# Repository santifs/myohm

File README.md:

# Myohm

Research and teaching platform for bioimpedance measurement: nRF5340, AD5941 and nPM1304.

**Research instrument, not a medical device. It has not been assessed against IEC 60601-1; measure people only within an ethics-approved research protocol, on battery power, after reading [Safety](#safety). Original hardware is licensed under CERN-OHL-S-2.0 and original software under Apache-2.0; bench data under CC-BY-4.0. Third-party libraries, models and vendor code keep their original terms; see [licence scope](LICENSE.md).**

| Component side | Rear silkscreen |
| :---: | :---: |
|  |  |

## Start here

- [Licence scope](LICENSE.md)
- [Engineering audit and blockers](docs/hardware-audit.md)
- [Licensing choices and third-party provenance](docs/licensing.md)
- [Validation and release gates](docs/validation.md)
- [Hardware sources](hardware/README.md)
- [Firmware](firmware/README.md) and [BLE protocol](firmware/nrf5340_zephyr/docs/ble-protocol.md)
- [Teaching laboratory](web/README.md)
- [Local-only iOS and Android clients](mobile/README.md)
- [Published Myohm workbench](https://lab.santiagofs.com/myohm/)

## Design and bench data

| Resource | Repository |
| --- | --- |
| Main board and electrode strips (75, 100, 150 mm; 50 mm designed) | `hardware/mainboard`, `hardware/electrodes` |
| Firmware, BLE protocol, sweep 4–198 kHz | `firmware/nrf5340_zephyr` |
| Bench procedure with the AD5940 impedance test board | `tools/bench/ztest.py` |
| Bench measurements | `tools/bench/data` (CC-BY-4.0) |
| Bench error model | `tools/bench/bench_error_model.py`, output `bench_error_model.json` |
| Nodal model of contact-impedance errors | `tools/bench/mismatch_model.py` |
| Sweep quality control, R/Xc and Cole fitting | `tools/analysis/myohm_spectra.py` |
| Android and iOS clients | `mobile/` |

## Interpreting a Cole fit

The Python analysis fits the real and imaginary parts of the aggregated impedance together.
Frequencies are in Hz, resistances are in ohms, and `tau_s` is in seconds.
In the denominator `1 + (j 2π f τ)^p`, use `p = cole_exponent`.
This is the exponent called alpha in the mobile models and the [Swarthmore MATLAB implementation](https://github.com/santifs/swarthmore/blob/2d40aa04922a031763f097dffae03454ec257618/matlab/Helpers%20Across%20Projects/fitColeColeModelMultiStartLevMar.m).
The Python field `alpha` retains the BioMess dispersion convention, so `p = 1 - alpha`.

Read `quality_flag` for repeat-sweep consistency, `success` for solver termination, and
`accepted` for the fit decision. A converged fit can still fail the acceptance criteria.
`rmse_pct` is 100 times the RMS complex residual divided by mean measured magnitude.
`cost_spread` is the range of solver costs across starts. It is not a parameter uncertainty.
The mobile optimizers use magnitude residuals. New mobile fit error percentages use the RMS
magnitude residual divided by mean measured magnitude, multiplied by 100. Older mobile
records can contain an ohm-valued residual in the percentage field. The quick mobile estimate
uses the sampled reactance peak and assumes an exponent of 0.8.

An unavailable Python estimate is JSON `null`; `failure_reason` explains a rejected fit.

## Safety

- The default excitation (800 mV peak-to-peak waveform, excitation-buffer gain 2) gives 1.6 V peak-to-peak behind 1 kΩ: up to 0.57 mA rms into a short circuit, and an output outside the ±607 mV range specified for the AD5941.
- The IEC 60601-1 patient auxiliary current limit for type BF parts (100 µA rms, rising with frequency above 1 kHz) is met by the short-circuit current only above about 5.7 kHz.
- For on-body use, build the firmware with `CONFIG_MYOHM_EXCITATION_MVPP=500` (0.35 mA rms into a short circuit). The default stays at 800 mV because the published bench data were acquired with it.
- Leakage, single-fault and charger behaviour have not been measured. Disconnect USB, SWD and bench instruments before connecting a person.
- Contact impedance limits accuracy. Several kilohms at a current electrode degrade the high-frequency phase, and kilohms at a voltage electrode can invalidate the measurement. The firmware's contact check (`0x0B`, see the [BLE protocol](firmware/nrf5340_zephyr/docs/ble-protocol.md)) is experimental and not yet validated on hardware.

## Repository layout

| Directory | Contents |
| --- | --- |
| `hardware/mainboard` | KiCad 10 project, schematic, PCB and local footprints |
| `hardware/3D` | Manufacturer component models, original terms |
| `hardware/library` | Recovered editable symbols and footprints |
| `firmware/nrf5340_zephyr` | Application and out-of-tree board; nRF Connect SDK 3.3.0 |
| `web` | React teaching lab, BLE transport and offline calculations |
| `mobile` | Native iOS and Android clients; local storage and explicit export |
| `docs` | Requirements, audit, provenance and release process |
| `tools` | Repository and hardware checks; `tools/bench` bench procedure, data and models; `tools/analysis` spectral analysis |
| `reports` | Review evidence, not production manufacturing files |

The repository starts from the corrected mainboard working tree and active firmware. The source candidate excludes experimental subject data, papers, experimental mobile applications, old nRF52832 hardware and build caches. Electrode fabrication exports are experimental review artifacts; no production mainboard Gerbers are supplied. See [source manifest](docs/import-manifest.json). Legacy identifiers (`AllInOne`, `BioMess`, `biomess_nrf5340`) remain where changing them would affect hardware revision identification or software compatibility. Myohm is the project name; a branding migration must preserve the BLE wire protocol.

## Checks

```sh
python3 tools/check_repository.py
python3 tools/verify_firmware_offline.py
python3 tools/check_hardware.py  # requires KiCad 10; ERC currently fails honestly
cd web
npm ci
npm test
npm run build
```

Source: https://github.com/santifs/myohm. A clean DRC is not electrical, RF, battery or human-use validation.

La [revisión eléctrica del 20 de septiembre](docs/electrical-review.md) registra las primeras correcciones de símbolos, las comprobaciones de integridad y las decisiones de diseño pendientes.

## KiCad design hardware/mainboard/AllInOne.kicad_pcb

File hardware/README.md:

# Myohm hardware

Current PCB v2 candidate: nRF5340 / AD5941 / nPM1304, imported from the `AllInOne-corrected` hardware working tree. This is not the old nRF52832/BQ24074 board.

Open `mainboard/AllInOne.kicad_pro` with KiCad 10.0.3 and standard KiCad 10 footprint/3D libraries installed. Project libraries use `${KIPRJMOD}`. Recovered symbols started from imported definitions; the electrical review records subsequent pin-type corrections. Editable does not mean fully validated. Footprint filters include the assigned KiCad names in addition to imported Altium names; this is metadata migration, not dimensional approval.

Firmware target: `biomess_nrf5340/nrf5340/cpuapp`. [Pinout](../firmware/nrf5340_zephyr/docs/hardware-v2.md), [audit](../docs/hardware-audit.md).

The historical `BOM.csv` is a reference only; use the generated schematic inventory in reports for review. Missing manufacturer part numbers and unknown battery remain release blockers. No production Gerbers are included, because inherited Gerbers predate the corrected board.

Original hardware contributions: **CERN-OHL-S-2.0**, with [scope and third-party exclusions](LICENSE.md).

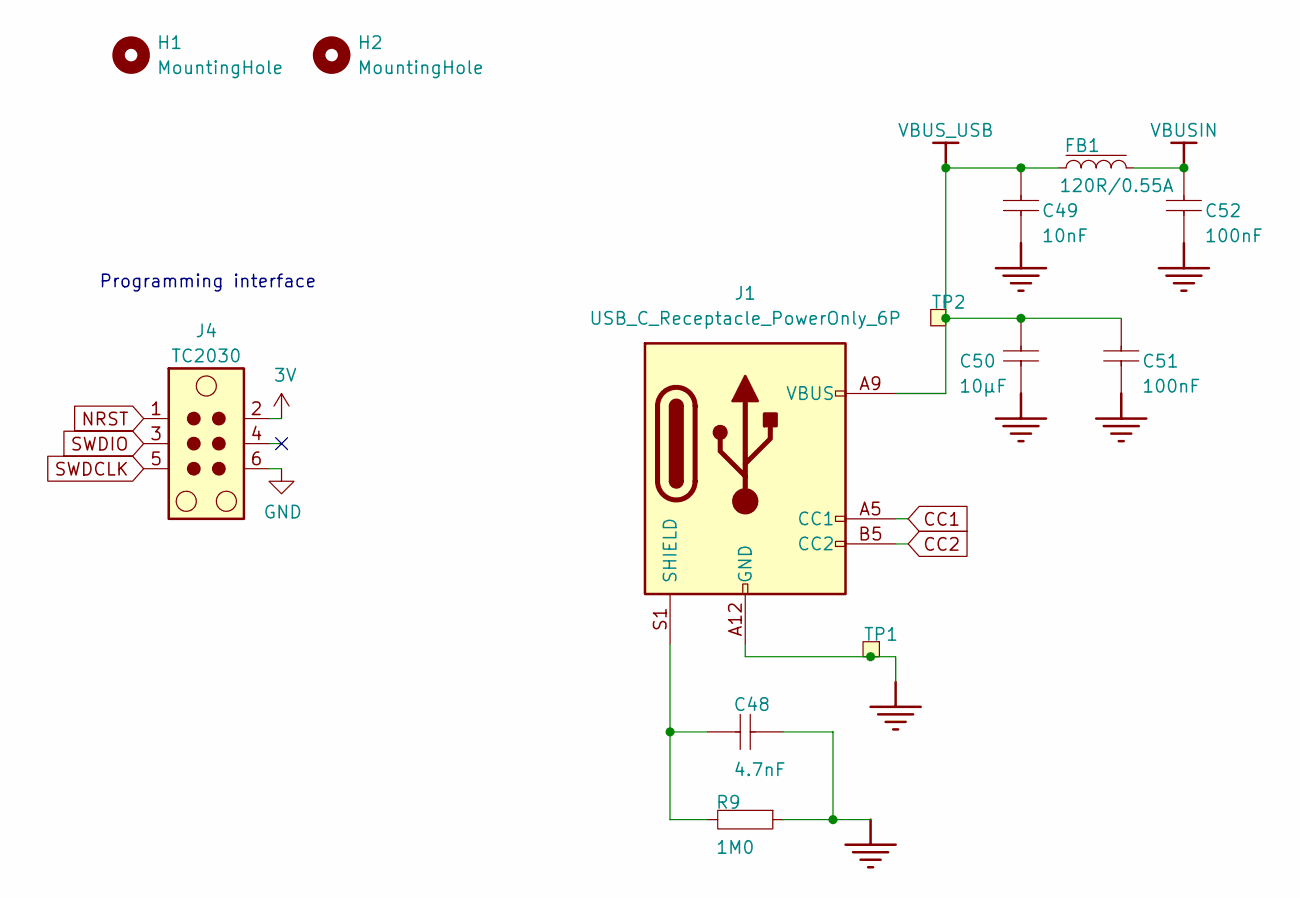
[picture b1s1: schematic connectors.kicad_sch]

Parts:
C48: 4.7nF; C_0201_0603Metric; PART NUMBER C0201-4n7-25V-X5R
C49: 10nF; C_0201_0603Metric; PART NUMBER C0201-10n-25V-X5R
C50: 10µF; C_0603_1608Metric; PART NUMBER C0603-10µ-25V-X5R-GRM188R61E106MA73J
C51, C52: 100nF; C_0201_0603Metric; PART NUMBER C0201-100n-25V-X5R
FB1: 120R/0.55A; L_0402_1005Metric; PART NUMBER FB0402-120R@100M-500mA
H1, H2: MountingHole; MountingHole_2.2mm_M2
J1: USB_C_Receptacle_PowerOnly_6P; USB_C_Receptacle_GCT_USB4135-GF-A_6P_TopMnt_Horizontal
J4: TC2030; Tag-Connect_TC2030-IDC-NL_2x03_P1.27mm_Vertical
R9: 1M0; R_0201_0603Metric; PART NUMBER R0201-1M0
TP1, TP2: Ø1.5mm,SMD; TestPoint_Pad_D1.5mm; PART NUMBER TP_SMD_Ø1.5MM

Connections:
AVDD_2: J4.2; also elsewhere on the board
CC1: J1.A5 (CC1); also elsewhere on the board
CC2: J1.B5 (CC2); also elsewhere on the board
GND: C48.2, C49.1, C50.1, C51.1, C52.1, J1.A12 (GND), J1.B12 (GND), J4.6, R9.2, TP1.1 (1_1); also elsewhere on the board
NRST: J4.1; also elsewhere on the board
unnamed: C48.1, J1.S1 (SHIELD), R9.1
SWDCLK: J4.5; also elsewhere on the board
SWDIO: J4.3; also elsewhere on the board
VBUSIN: C52.2, FB1.2; also elsewhere on the board
VBUS_USB: C49.2, C50.2, C51.2, FB1.1, J1.A9 (VBUS), J1.B9 (VBUS), TP2.1 (1_1)

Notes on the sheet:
Programming interface

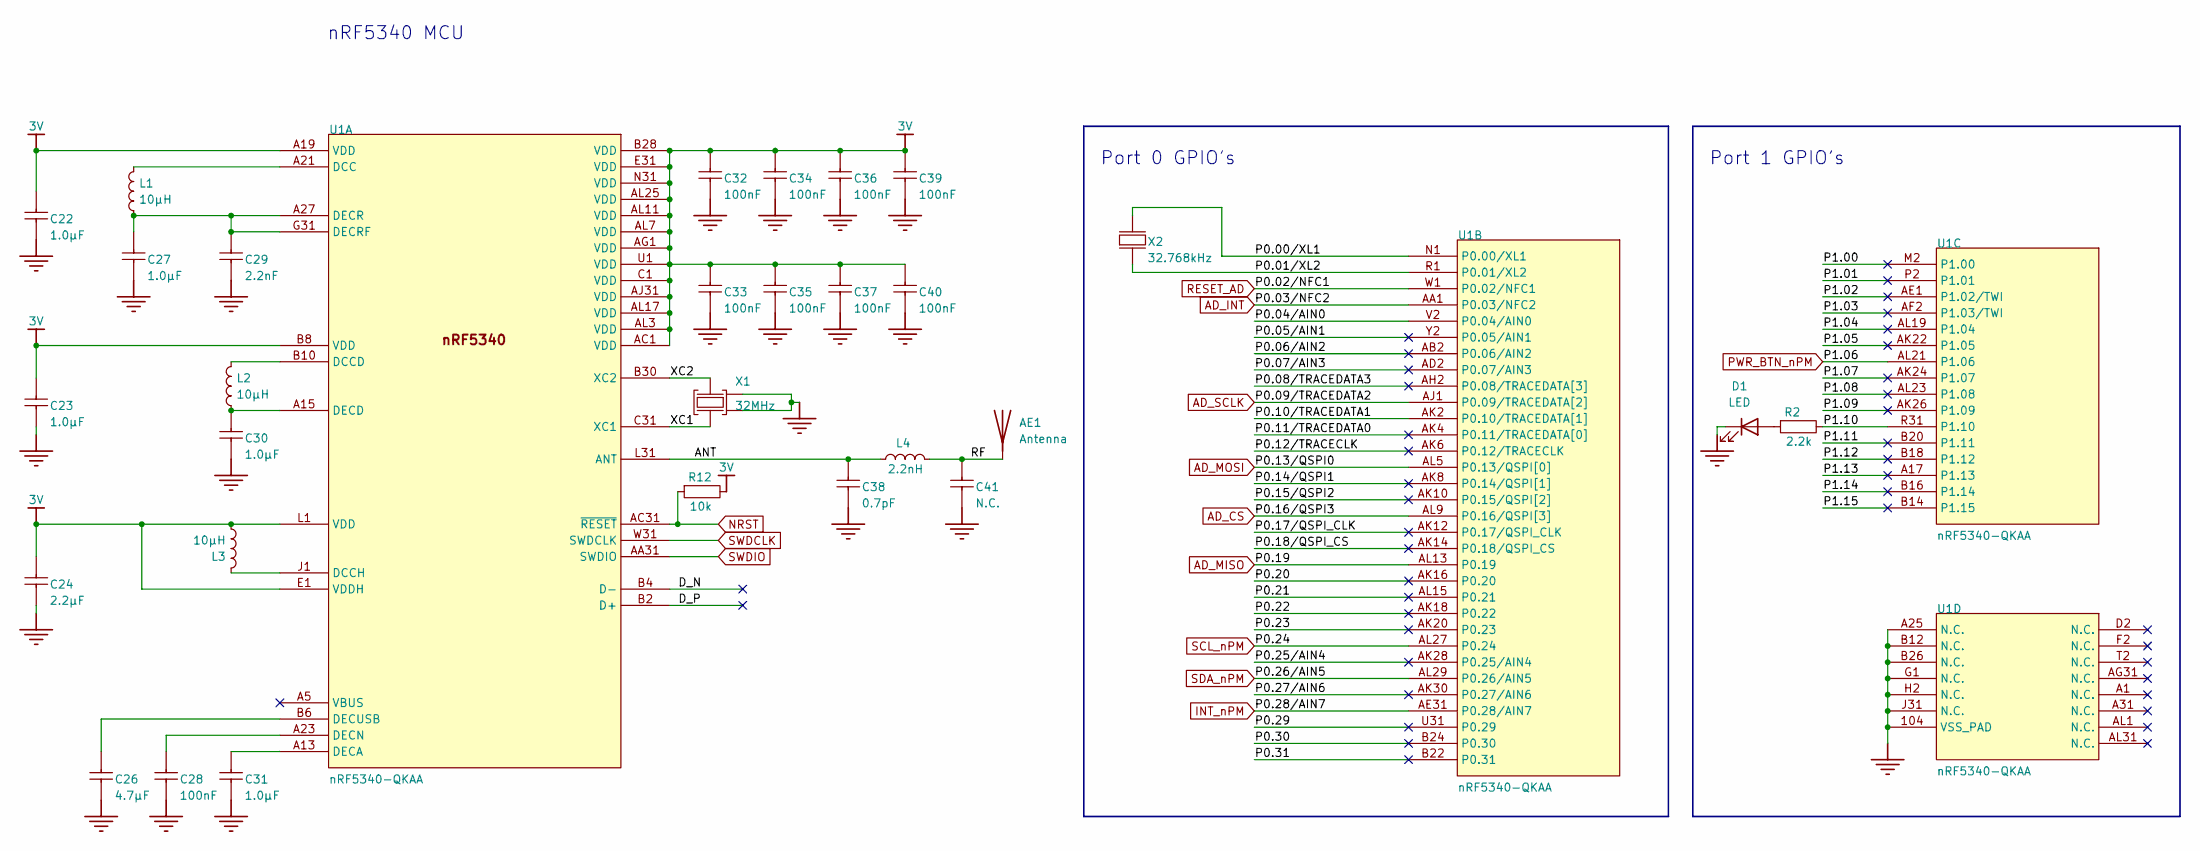
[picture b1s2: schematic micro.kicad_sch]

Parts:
AE1: Antenna; Johanson_2450AT18x100
C22, C23, C27, C30, C31: 1.0µF; C_0402_1005Metric; PART NUMBER C0402-1µ0-25V-X5R
C24: 2.2µF; C_0402_1005Metric; PART NUMBER C0402-1µ0-25V-X5R
C26: 4.7µF; C_0603_1608Metric; PART NUMBER C0603-4µ7-25V-X5R
C28, C32, C33, C34, C35, C36, C37, C39, C40: 100nF; C_0201_0603Metric; PART NUMBER C0201-100n-6.3V-X5R
C29: 2.2nF; C_0201_0603Metric; PART NUMBER C0201-2n2-10V-X5R
C38: 0.7pF; C_0201_0603Metric; PART NUMBER C0201-0.7p-50V-C0G-GJM0335C1HR70WB01
C41: N.C.; C_0402_1005Metric; PART NUMBER C0201-N.C.
D1: LED; LED_0603_1608Metric
L1, L2, L3: 10µH; L_0603_1608Metric; PART NUMBER L0603-10µ-Murata-DN
L4: 2.2nH; L_0201_0603Metric; PART NUMBER L0201-2n2-HQ-Murata
R2: 2.2k; R_0402_1005Metric; MANUFACTURER PART NUMBER N.A.
R12: 10k; R_0201_0603Metric; PART NUMBER R0201-47k
U1: nRF5340-QKAA; nRF5340-QKAA-Messi; PART NUMBER nRF5340-QKAAD0
X1: 32MHz; Crystal_SMD_2016-4Pin_2.0x1.6mm; PART NUMBER XRCGB32M000F1S1BR0
X2: 32.768kHz; Crystal_SMD_2012-2Pin_2.0x1.2mm; PART NUMBER XTAL_SMD2012_32.768kHz_9pF_MC

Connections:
/Micro/ANT: C38.2, L4.2, U1.L31 (ANT)
/Micro/D_N: U1.B4 (D-)
/Micro/D_P: U1.B2 (D+)
/Micro/P0.00/XL1: U1.N1 (P0.00/XL1), X2.1 (inp)
/Micro/P0.01/XL2: U1.R1 (P0.01/XL2), X2.2 (out)
/Micro/P0.04/AIN0: U1.V2 (P0.04/AIN0)
/Micro/P0.05/AIN1: U1.Y2 (P0.05/AIN1)
/Micro/P0.06/AIN2: U1.AB2 (P0.06/AIN2)
/Micro/P0.07/AIN3: U1.AD2 (P0.07/AIN3)
/Micro/P0.08/TRACEDATA3: U1.AH2 (P0.08/TRACEDATA[3])
/Micro/P0.10/TRACEDATA1: U1.AK2 (P0.10/TRACEDATA[1])
/Micro/P0.11/TRACEDATA0: U1.AK4 (P0.11/TRACEDATA[0])
/Micro/P0.12/TRACECLK: U1.AK6 (P0.12/TRACECLK)
/Micro/P0.14/QSPI1: U1.AK8 (P0.14/QSPI[1])
/Micro/P0.15/QSPI2: U1.AK10 (P0.15/QSPI[2])
/Micro/P0.17/QSPI_CLK: U1.AK12 (P0.17/QSPI_CLK)
/Micro/P0.18/QSPI_CS: U1.AK14 (P0.18/QSPI_CS)
/Micro/P0.20: U1.AK16 (P0.20)
/Micro/P0.21: U1.AL15 (P0.21)
/Micro/P0.22: U1.AK18 (P0.22)
/Micro/P0.23: U1.AK20 (P0.23)
/Micro/P0.25/AIN4: U1.AK28 (P0.25/AIN4)
/Micro/P0.27/AIN6: U1.AK30 (P0.27/AIN6)
/Micro/P0.29: U1.U31 (P0.29)
/Micro/P0.30: U1.B24 (P0.30)
/Micro/P0.31: U1.B22 (P0.31)
/Micro/P1.00: U1.M2 (P1.00)
/Micro/P1.01: U1.P2 (P1.01)
/Micro/P1.02: U1.AE1 (P1.02/TWI)
/Micro/P1.03: U1.AF2 (P1.03/TWI)
/Micro/P1.04: U1.AL19 (P1.04)
/Micro/P1.05: U1.AK22 (P1.05)
/Micro/P1.07: U1.AK24 (P1.07)
/Micro/P1.08: U1.AL23 (P1.08)
/Micro/P1.09: U1.AK26 (P1.09)
/Micro/P1.10: R2.1, U1.R31 (P1.10)
/Micro/P1.11: U1.B20 (P1.11)
/Micro/P1.12: U1.B18 (P1.12)
/Micro/P1.13: U1.A17 (P1.13)
/Micro/P1.14: U1.B16 (P1.14)
/Micro/P1.15: U1.B14 (P1.15)
/Micro/RF: AE1.1 (A_1), C41.2, L4.1
/Micro/XC1: U1.C31 (XC1), X1.1 (IN)
/Micro/XC2: U1.B30 (XC2), X1.3 (OUT)
AD_CS: U1.AL9 (P0.16/QSPI[3]); also elsewhere on the board
AD_INT: U1.AA1 (P0.03/NFC2); also elsewhere on the board
AD_MISO: U1.AL13 (P0.19); also elsewhere on the board
AD_MOSI: U1.AL5 (P0.13/QSPI[0]); also elsewhere on the board
AD_SCLK: U1.AJ1 (P0.09/TRACEDATA[2]); also elsewhere on the board
AVDD_2: C22.1, C23.2, C24.2, C32.1, C33.1, C34.1, C35.1, C36.1, C37.1, C39.1, C40.1, L3.1, R12.1, U1.A19 (VDD), U1.AC1 (VDD), U1.AG1 (VDD), U1.AJ31 (VDD), U1.AL3 (VDD), U1.AL7 (VDD), U1.AL11 (VDD), U1.AL17 (VDD), U1.AL25 (VDD), U1.B8 (VDD), U1.B28 (VDD), U1.C1 (VDD), U1.E1 (VDDH), U1.E31 (VDD), U1.L1 (VDD), U1.N31 (VDD), U1.U1 (VDD); also elsewhere on the board
GND: C22.2, C23.1, C24.1, C26.2, C27.1, C28.2, C29.2, C30.1, C31.1, C32.2, C33.2, C34.2, C35.2, C36.2, C37.2, C38.1, C39.2, C40.2, C41.1, D1.1 (K), U1.104 (VSS_PAD), U1.A25 (N.C.), U1.B12 (N.C.), U1.B26 (N.C.), U1.G1 (N.C.), U1.H2 (N.C.), U1.J31 (N.C.), X1.2 (GND), X1.4 (GND); also elsewhere on the board
INT_nPM: U1.AE31 (P0.28/AIN7); also elsewhere on the board
NRST: R12.2, U1.AC31 (~RESET); also elsewhere on the board
unnamed: D1.2 (A), R2.2
unnamed: L1.2, U1.A21 (DCC)
unnamed: L2.2, U1.B10 (DCCD)
unnamed: L3.2, U1.J1 (DCCH)
unnamed: C31.2, U1.A13 (DECA)
unnamed: C30.2, L2.1, U1.A15 (DECD)
unnamed: C28.1, U1.A23 (DECN)
unnamed: C27.2, C29.1, L1.1, U1.A27 (DECR), U1.G31 (DECRF)
unnamed: C26.1, U1.B6 (DECUSB)
PWR_BTN_nPM: U1.AL21 (P1.06); also elsewhere on the board
RESET_AD: U1.W1 (P0.02/NFC1); also elsewhere on the board
SCL_nPM: U1.AL27 (P0.24); also elsewhere on the board
SDA_nPM: U1.AL29 (P0.26/AIN5); also elsewhere on the board
SWDCLK: U1.W31 (SWDCLK); also elsewhere on the board
SWDIO: U1.AA31 (SWDIO); also elsewhere on the board

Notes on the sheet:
Port 0 GPIO's
Port 1 GPIO's
nRF5340 MCU

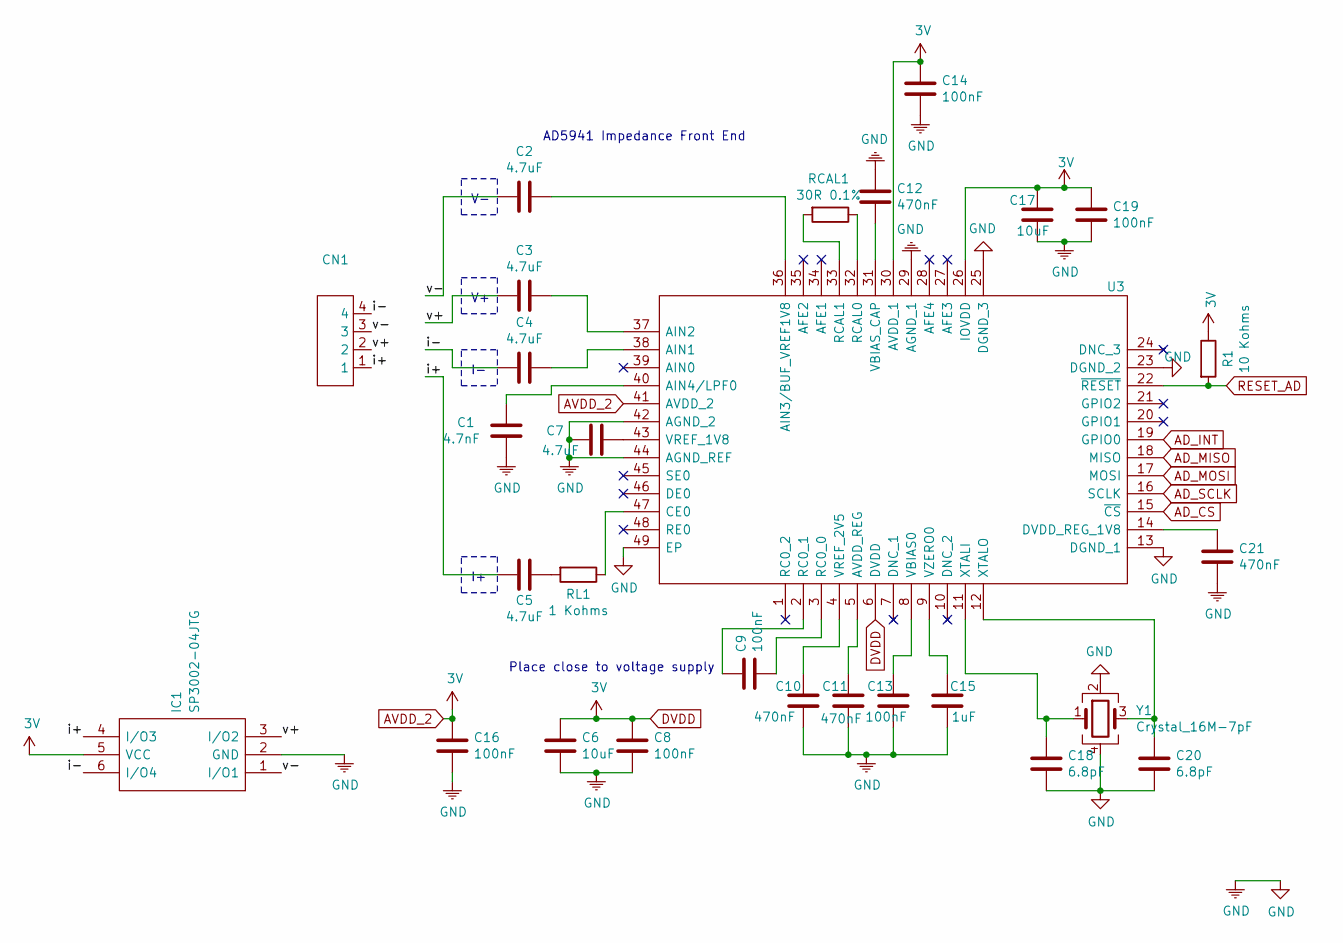
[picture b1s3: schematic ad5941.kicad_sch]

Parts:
C1: 4.7nF; C_0603_1608Metric
C2, C3, C4, C5, C7: 4.7uF; C_0603_1608Metric
C6, C17: 10uF; C_0402_1005Metric
C8, C9, C13, C14, C16, C19: 100nF; C_0402_1005Metric
C10, C11, C12, C21: 470nF; C_0402_1005Metric
C15: 1uF; C_0402_1005Metric
C18, C20: 6.8pF; C_0402_1005Metric
CN1: POGO-TH_PR5L3715-4P-C-male; Manufacturer Part PR5L3715-4P-C-H; LCSC Part Name 2.54-4P磁吸弹簧探针连接器超薄公头POGOPIN适配PR5L2820-4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
IC1: SP3002-04JTG; SOT-363_SC-70-6; Manufacturer_Part_Number SP3002-04JTG
R1: 10 Kohms; R_0402_1005Metric
RCAL1: 30R 0.1%; R_0402_1005Metric
RL1: 1 Kohms; R_0402_1005Metric
U3: AD5941BCPZ; QFN50P700X700X80-49N-D; Manufacturer_Part_Number AD5941BCPZ
Y1: Crystal_16M-7pF; Crystal_SMD_Abracon_ABM8G-4Pin_3.2x2.5mm

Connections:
/AD5941/i+: C5.2, CN1.1, IC1.4 (I/O3)
/AD5941/i-: C4.2, CN1.4, IC1.6 (I/O4)
/AD5941/v+: C3.2, CN1.2, IC1.3 (I/O2)
/AD5941/v-: C2.2, CN1.3, IC1.1 (I/O1)
AD_CS: U3.15 (~CS); also elsewhere on the board
AD_INT: U3.19 (GPIO0); also elsewhere on the board
AD_MISO: U3.18 (MISO); also elsewhere on the board
AD_MOSI: U3.17 (MOSI); also elsewhere on the board
AD_SCLK: U3.16 (SCLK); also elsewhere on the board
AVDD_2: C6.1, C8.1, C14.1, C16.1, C17.1, C19.1, IC1.5 (VCC), R1.1, U3.6 (DVDD), U3.26 (IOVDD), U3.30 (AVDD_1), U3.41 (AVDD_2); also elsewhere on the board
GND: C1.2, C6.2, C7.2, C8.2, C10.2, C11.2, C12.1, C13.2, C14.2, C15.2, C16.2, C17.2, C18.2, C19.2, C20.2, C21.2, IC1.2 (GND), U3.13 (DGND_1), U3.23 (DGND_2), U3.25 (DGND_3), U3.29 (AGND_1), U3.42 (AGND_2), U3.44 (AGND_REF), U3.49 (EP), Y1.2, Y1.4; also elsewhere on the board
unnamed: C5.1, RL1.2
unnamed: C4.1, U3.38 (AIN1)
unnamed: C3.1, U3.37 (AIN2)
unnamed: C2.1, U3.36 (AIN3/BUF_VREF1V8)
unnamed: C1.1, U3.40 (AIN4/LPF0)
unnamed: C11.1, U3.5 (AVDD_REG)
unnamed: RL1.1, U3.47 (CE0)
unnamed: C21.1, U3.14 (DVDD_REG_1V8)
unnamed: C9.2, U3.3 (RC0_0)
unnamed: C9.1, U3.2 (RC0_1)
unnamed: RCAL1.1, U3.32 (RCAL0)
unnamed: RCAL1.2, U3.33 (RCAL1)
unnamed: C13.1, U3.8 (VBIAS0)
unnamed: C12.2, U3.31 (VBIAS_CAP)
unnamed: C7.1, U3.43 (VREF_1V8)
unnamed: C10.1, U3.4 (VREF_2V5)
unnamed: C15.1, U3.9 (VZERO0)
unnamed: C18.1, U3.11 (XTALI), Y1.1
unnamed: C20.1, U3.12 (XTALO), Y1.3
RESET_AD: R1.2, U3.22 (~RESET); also elsewhere on the board

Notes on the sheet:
Place close to voltage supply
AD5941 Impedance Front End

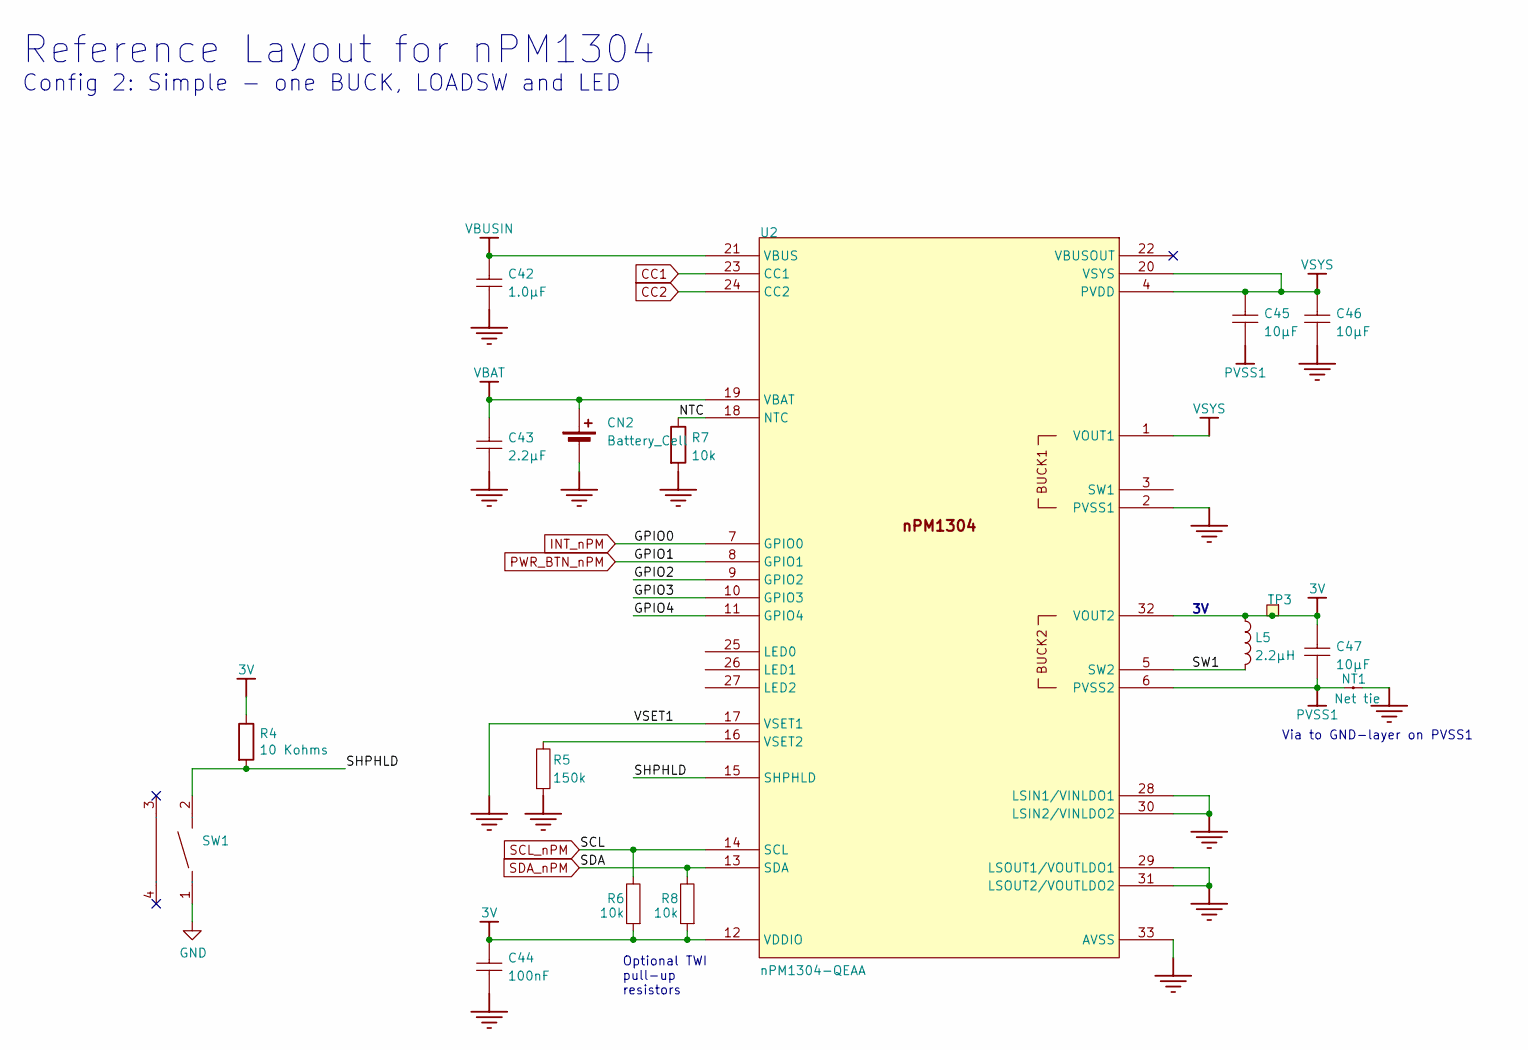
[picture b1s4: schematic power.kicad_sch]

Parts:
C42: 1.0µF; C_0603_1608Metric; PART NUMBER C0603-1µ0-25V-X5R
C43: 2.2µF; C_0603_1608Metric; PART NUMBER C0603-2µ2-25V-X5R-GRM188R61E225KA12D
C44: 100nF; C_0201_0603Metric; PART NUMBER C0201-100n-25V-X5R
C45, C46, C47: 10µF; C_0603_1608Metric; PART NUMBER C0603-10µ-10V-X5R
CN2: Battery_Cell; JST_PH_S2B-PH-SM4-TB_1x02-1MP_P2.00mm_Horizontal
L5: 2.2µH; L_0805_2012Metric_Pad1.05x1.20mm_HandSolder; PART NUMBER L0806-2µ2-2500mA-73mOhm-CIGT201610EH2R2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
NT1: Net tie; NetTie-2_SMD_Pad0.5mm; PART NUMBER 2 pin starpoint
R4: 10 Kohms; C_0402_1005Metric
R5: 150k; R_0201_0603Metric; PART NUMBER R0201-47k
R6, R8: 10k; R_0201_0603Metric; PART NUMBER R0201-10k
R7: 10k; R_0402_1005Metric_Pad0.72x0.64mm_HandSolder
SW1: SW-SMD_2P-TS24CA; Manufacturer Part TS24CA; LCSC Part Name 4.55*1.8*3.5mm 卧贴 轻触开关
TP3: Ø1.5mm,SMD; TestPoint_Pad_D1.5mm; PART NUMBER TP_SMD_Ø1.5MM
U2: nPM1304-QEAA; QFN50P500X500X90-33N; PART NUMBER nPM1304-QEAA

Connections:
/Power/GPIO2: U2.9 (GPIO2)
/Power/GPIO3: U2.10 (GPIO3)
/Power/GPIO4: U2.11 (GPIO4)
/Power/NTC: R7.1, U2.18 (NTC)
/Power/SHPHLD: R4.2, SW1.2, U2.15 (SHPHLD)
/Power/SW1: L5.2, U2.5 (SW2)
AVDD_2: C44.1, C47.2, L5.1, R4.1, R6.2, R8.2, TP3.1 (1_1), U2.12 (VDDIO), U2.32 (VOUT2); also elsewhere on the board
CC1: U2.23 (CC1); also elsewhere on the board
CC2: U2.24 (CC2); also elsewhere on the board
GND: C42.1, C43.1, C44.2, C46.1, CN2.2 (-), NT1.1, R5.2, R7.2, SW1.1, U2.2 (PVSS1), U2.17 (VSET1), U2.28 (LSIN1/VINLDO1), U2.29 (LSOUT1/VOUTLDO1), U2.30 (LSIN2/VINLDO2), U2.31 (LSOUT2/VOUTLDO2), U2.33 (AVSS); also elsewhere on the board
INT_nPM: U2.7 (GPIO0); also elsewhere on the board
unnamed: R5.1, U2.16 (VSET2)
PVSS1: C45.1, C47.1, NT1.2, U2.6 (PVSS2)
PWR_BTN_nPM: U2.8 (GPIO1); also elsewhere on the board
SCL_nPM: R6.1, U2.14 (SCL); also elsewhere on the board
SDA_nPM: R8.1, U2.13 (SDA); also elsewhere on the board
VBAT: C43.2, CN2.1 (+), U2.19 (VBAT)
VBUSIN: C42.2, U2.21 (VBUS); also elsewhere on the board
VSYS: C45.2, C46.2, U2.1 (VOUT1), U2.4 (PVDD), U2.20 (VSYS)

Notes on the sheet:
Reference Layout for nPM1304
Config 2: Simple - one BUCK, LOADSW and LED
Via to GND-layer on PVSS1
Optional TWI pull-up resistors

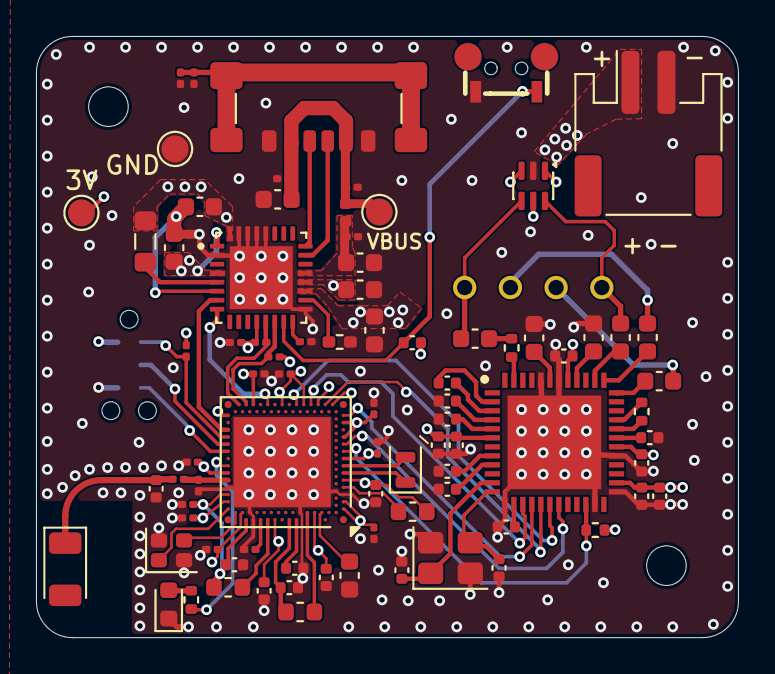
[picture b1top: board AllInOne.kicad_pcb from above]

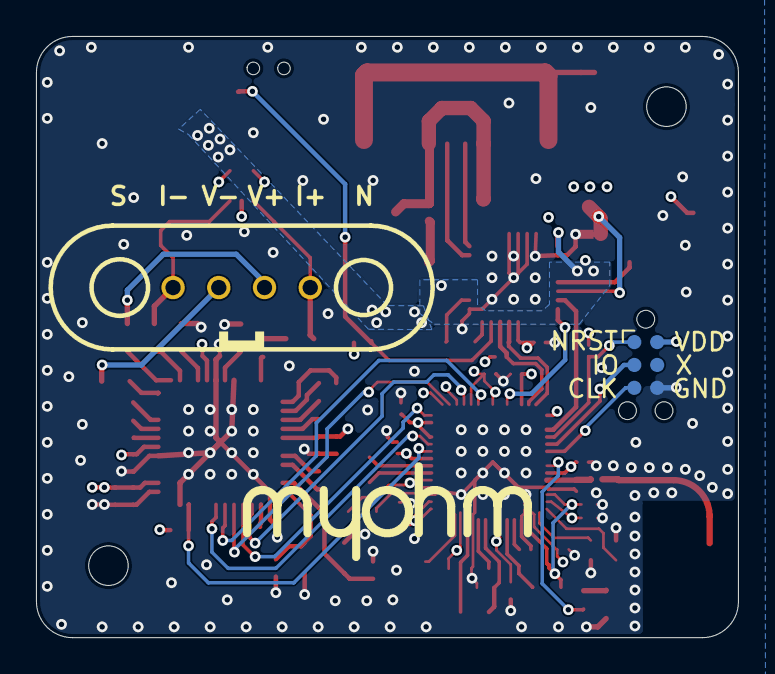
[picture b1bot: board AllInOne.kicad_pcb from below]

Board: 4 copper layers, 39.0 x 33.4 mm, 88 parts (2 on the bottom side), 66 nets.

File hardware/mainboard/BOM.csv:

Comment,Designator,Footprint,JLCPCB Part #（optional）
100nF,"C33,C28,C32,C35,C34,C36,C39,C40,C37,C51,C44,C52",0201,C76934
2.2uF,C24,0402,C12530
1.0uF,"C31,C30,C22,C27,C23",0402,C52923
LED,D1,0603,C2290
4.7uF,C26,0603,C19666
10uH,"L3,L2,L1",0603,C1035
0.7pF,C38,0201,C161449
32.768kHz,X2,Crystal_SMD_2012-2Pin_2.0x1.2mm,C97606
2.2nF,C29,0201,C80433
32MHz,X1,Crystal_SMD_2016-4Pin_2.0x1.6mm,C843260
2.2nH,L4,0201,C98041
2.2k,R2,0402,C25879
nRF5340-QKAA,U1,Nordic_AQFN-94-1EP_7x7mm_P0.4mm,C3015611
10k,"R12,R6,R8",0201,C7467266
2.4GHz Chip Antenna,AE1,Johanson_2450AT18x100,C89334
Ferrite Bead 120R 0.55A,FB1,0402,C76891
100nF,"C19,C14,C16,C8,C9,C13",0402,C1525
1uF,C15,0402,C52923
150k,R5,0201,C310173
4.7uF,"C2,C7,C3,C5,C4",0603,C19666
JST PH 2P,CN2,JST_PH_S2B-PH-SM4-TB_1x02-1MP_P2.00mm_Horizontal,C295747
10k,R1,0402,C25744
10k,R4,0402,C25744
Switch SPST,SW1,SW-SMD_2P-TS24CA,C393942
USB_C_Receptacle_6P,J1,USB_C_Receptacle_GCT_USB4135-GF-A_6P_TopMnt_Horizontal,C5438410
470nF,"C11,C21,C12,C10",0402,C47339
4.7nF,C1,0603,C53987
10uF,"C50,C46,C47,C45",0603,C19702
AD5941BCPZ,U3,QFN50P700X700X80-49N-D,C503573
10nF,C49,0201,C285010
2.2uF,C43,0603,C23630
1.0uF,C42,0603,C15849
30R 0.1%,RCAL1,0402,C852718
6.8pF,"C18,C20",0402,C1576
10k,R7,0402,C25744
4.7nF,C48,0201,C42437895
10uF,"C17,C6",0402,C15525
nPM1304-QEAA,U2,QFN50P500X500X90-33N,C49448846
1M0,R9,0201,C473450
16MHz,Y1,Crystal_SMD_Abracon_ABM8G-4Pin_3.2x2.5mm,C880097
2.2uH,L5,0805,C1043
1k,RL1,0402,
SP3002-04JTG,IC1,SOT-363_SC-70-6,

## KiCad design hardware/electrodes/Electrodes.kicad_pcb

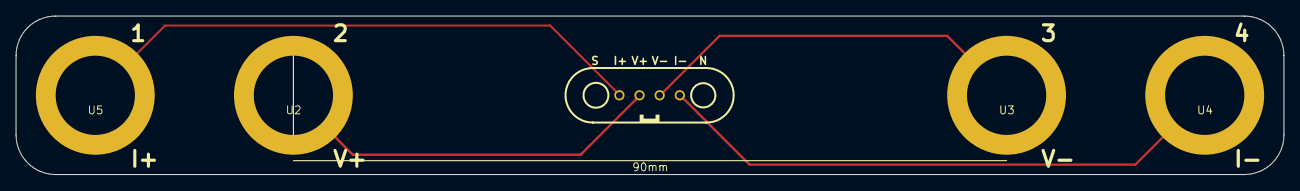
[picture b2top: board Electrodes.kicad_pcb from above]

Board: 2 copper layers, 160.0 x 20.0 mm, 5 parts (0 on the bottom side), 4 nets.

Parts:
CN1: POGO-TH_PR5L2820-4P-C-F-female
U2, U3, U4, U5: ECG_Electrode

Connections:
/i+: CN1.4, U5.1 (1_1)
/i-: CN1.1, U4.1 (1_1)
/v+: CN1.3, U2.1 (1_1)
/v-: CN1.2, U3.1 (1_1)
